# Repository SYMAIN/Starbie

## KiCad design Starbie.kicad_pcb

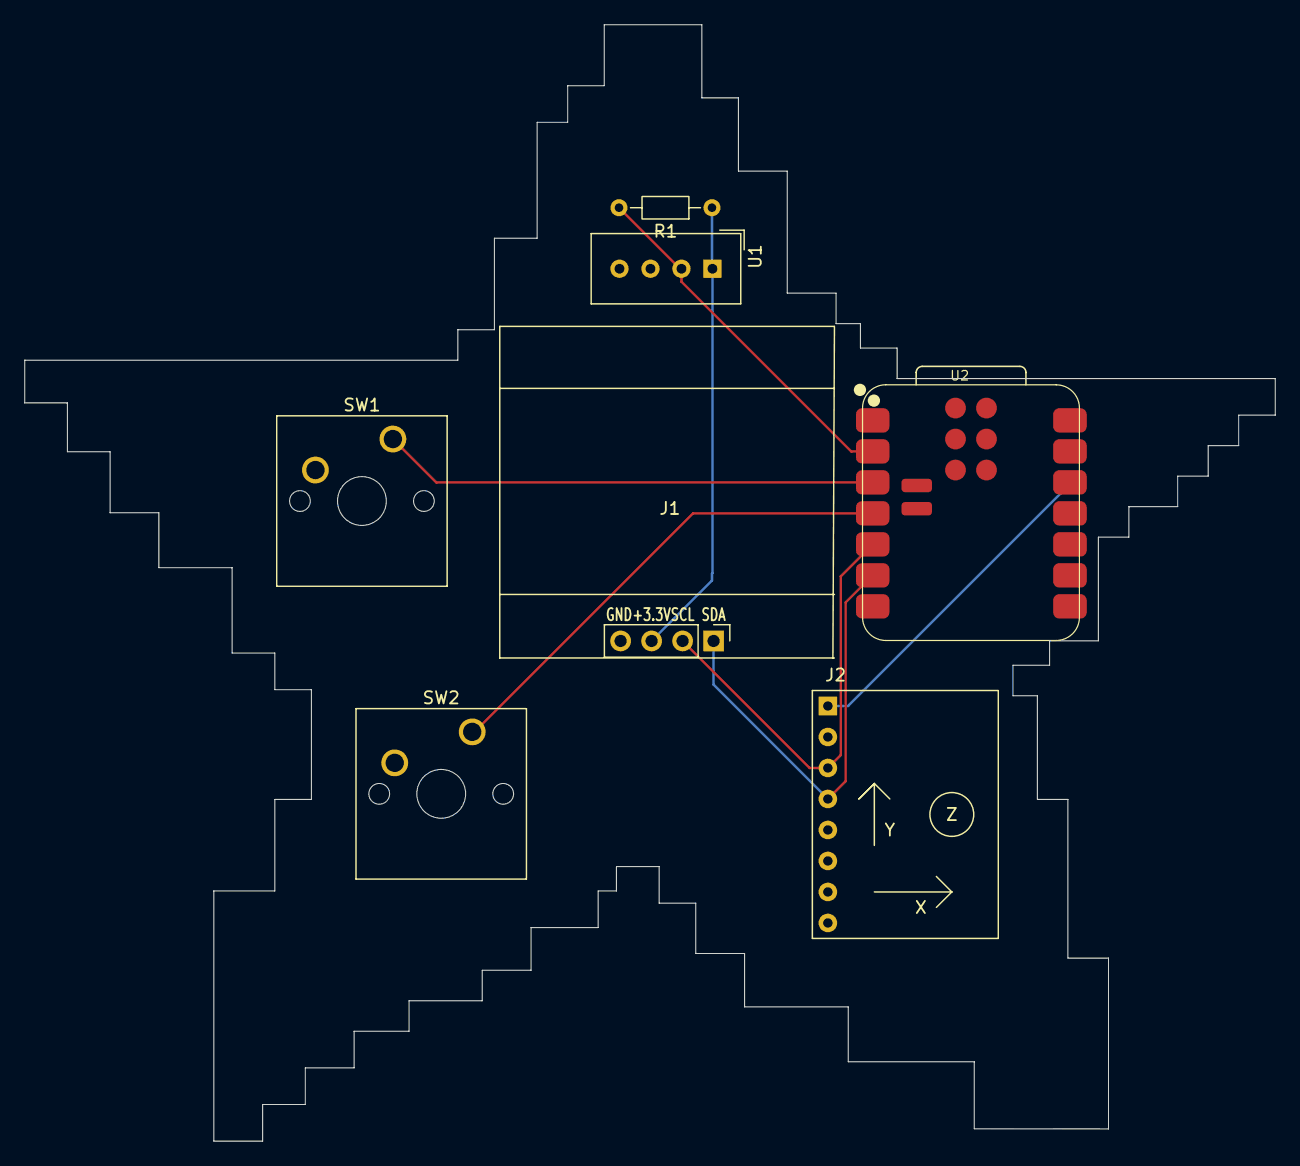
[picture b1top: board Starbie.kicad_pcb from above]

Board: 2 copper layers, 102.5 x 91.5 mm, 7 parts (0 on the bottom side), 7 nets.

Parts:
J1: Conn_01x04_Pin; Display_128x64_096_I2C
J2: Conn_01x08_Pin; MPU6050_Module
R1: 10k; R_Axial_DIN0204_L3.6mm_D1.6mm_P7.62mm_Horizontal
SW1, SW2: SW_Push; SW_Cherry_MX_1.00u_PCB
U1: DHT11; Aosong_DHT11_5.5x12.0_P2.54mm
U2: XIAO-ESP32-C3-SMD

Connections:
+3.3V: J1.3, J2.1, R1.1, U1.1 (VDD), U2.12 (3V3_OUT)
/DHT11 DATA: R1.2, U1.2 (DATA), U2.2 (D1)
/GPIO2: SW1.1, U2.3 (D2)
/GPIO3: SW2.1, U2.4 (D3)
/SCL: J1.2, J2.3, U2.5 (D4)
/SDA: J1.1, J2.4, U2.6 (D5)
GND: J1.4, J2.2, SW1.2, SW2.2, U1.4 (GND), U2.13 (GND), U2.18 (GND)
